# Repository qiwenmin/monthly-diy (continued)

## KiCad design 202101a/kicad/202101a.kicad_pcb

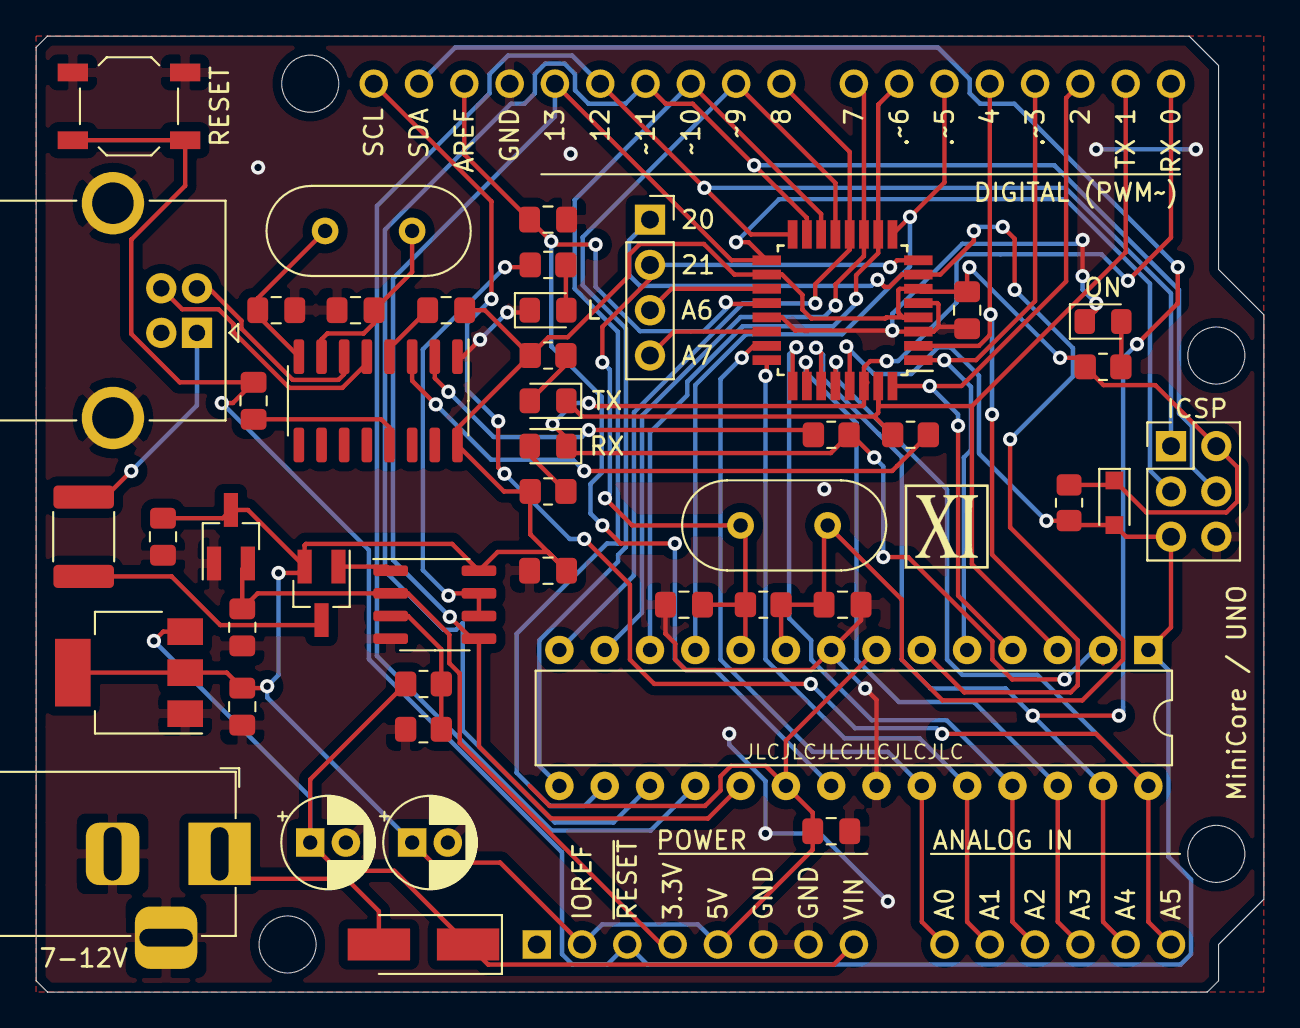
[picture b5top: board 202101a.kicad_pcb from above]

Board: 2 copper layers, 68.8 x 53.6 mm, 47 parts (1 on the bottom side), 48 nets.

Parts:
A1: Arduino_UNO_R3_BOARD; Arduino_UNO_R3_WithMountingHoles
C1, C2: 47u; CP_Radial_D5.0mm_P2.00mm
C3, C4, C5, C6, C9, C10, C11, C14, C15: 100n; C_0805_2012Metric_Pad1.18x1.45mm_HandSolder
C7, C8, C12, C13: 22p; C_0805_2012Metric_Pad1.18x1.45mm_HandSolder
D1: M7; D_SMA_Handsoldering
D2: ON; LED_0805_2012Metric_Pad1.15x1.40mm_HandSolder
D3: 1N4148WS; D_SOD-323_HandSoldering
D4: RX; LED_0805_2012Metric_Pad1.15x1.40mm_HandSolder
D5: TX; LED_0805_2012Metric_Pad1.15x1.40mm_HandSolder
D6: L; LED_0805_2012Metric_Pad1.15x1.40mm_HandSolder
F1: 500mA; Fuse_1812_4532Metric_Pad1.30x3.40mm_HandSolder
J1: Barrel_Jack_Switch; BarrelJack_Horizontal
J2: USB_B; USB_B_OST_USB-B1HSxx_Horizontal
J3: ICSP; PinHeader_2x03_P2.54mm_Vertical
J4: ExtIO; PinSocket_1x04_P2.54mm_Vertical
Q1: DMG2301L; SOT-23_Handsoldering
R1, R6, R7, R8, R9: 4.7K; R_0805_2012Metric_Pad1.20x1.40mm_HandSolder
R2, R3: 10K; R_0805_2012Metric_Pad1.20x1.40mm_HandSolder
R4, R5: 1K; R_0805_2012Metric_Pad1.20x1.40mm_HandSolder
R10: 1M; R_0805_2012Metric_Pad1.20x1.40mm_HandSolder
SW1: RESET; SW_SPST_TL3342
U1: AMS1117-5.0; SOT-223-3_TabPin2
U2: XC6206P332MR; SOT-23_Handsoldering
U3: LM358; SOIC-8_3.9x4.9mm_P1.27mm
U4: CH340G; SOIC-16_3.9x9.9mm_P1.27mm
U5: ATmega328-PU; DIP-28_W7.62mm
U6: ATmega328-AU; TQFP-32_7x7mm_P0.8mm
Y1: 12MHz; Crystal_HC49-4H_Vertical
Y2: 16MHz; Crystal_HC49-4H_Vertical

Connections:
+3V3: A1.4, C5.1, U2.2, U3.2
+5V: A1.2, A1.5, C2.1, C3.1, C4.1, C6.1, C9.1, C14.2, C15.2, D3.1, J3.2, Q1.2, R1.1, R6.1, R7.1, R8.1, U1.2, U2.3, U3.8, U4.16, U5.7, U5.20, U6.4, U6.6, U6.18
/A0: A1.9, U5.23, U6.23
/A1: A1.10, U5.24, U6.24
/A2: A1.11, U5.25, U6.25
/A3: A1.12, U5.26, U6.26
/A6: J4.3, U6.19
/A7: J4.4, U6.22
/AREF: A1.30, C11.1, U5.21, U6.20
/CMP: R2.2, R3.1, U3.3
/D0_RX: A1.15, D4.1, R4.1, U5.2, U6.30
/D1_TX: A1.16, D5.1, R5.1, U5.3, U6.31
/D2: A1.17, U5.4, U6.32
/D3: A1.18, U5.5, U6.1
/D4: A1.19, U5.6, U6.2
/D5: A1.20, U5.11, U6.9
/D6: A1.21, U5.12, U6.10
/D7: A1.22, U5.13, U6.11
/D8: A1.23, U5.14, U6.12
/D9: A1.24, U5.15, U6.13
/D10: A1.25, U5.16, U6.14
/D11: A1.26, J3.4, U5.17, U6.15
/D12: A1.27, J3.1, U5.18, U6.16
/D13: A1.28, J3.3, U3.5, U5.19, U6.17
/D20: C13.1, J4.1, R10.1, U5.9, U6.7, Y2.2
/D21: C12.1, J4.2, R10.2, U5.10, U6.8, Y2.1
/SCL_A5: A1.14, A1.32, U5.28, U6.28
/SDA_A4: A1.13, A1.31, U5.27, U6.27
/USBVCC: F1.1, Q1.3
/VIN: A1.8, C1.1, D1.1, R2.1, U1.3
/~RESET: A1.3, C10.1, D3.2, J3.5, R6.2, SW1.2, U5.1, U6.29
GND: A1.6, A1.7, A1.29, C1.2, C2.2, C3.2, C4.2, C5.2, C6.2, C7.2, C8.2, C11.2, C12.2, C13.2, C14.1, C15.1, D2.1, D6.1, J1.2, J1.3, J2.4, J2.5, J3.6, R3.2, SW1.1, U1.1, U2.1, U3.4, U4.1, U5.8, U5.22, U6.3, U6.5, U6.21
unnamed: C7.1, U4.7, Y1.1
unnamed: C8.1, U4.8, Y1.2
unnamed: C9.2, U4.4
unnamed: C10.2, U4.13
unnamed: D1.2, J1.1
unnamed: D2.2, R1.2
unnamed: D4.2, R7.2
unnamed: D5.2, R8.2
unnamed: D6.2, R9.1
unnamed: F1.2, J2.1
unnamed: J2.2, U4.6
unnamed: J2.3, U4.5
unnamed: Q1.1, U3.1
unnamed: R4.2, U4.2
unnamed: R5.2, U4.3
unnamed: R9.2, U3.6, U3.7

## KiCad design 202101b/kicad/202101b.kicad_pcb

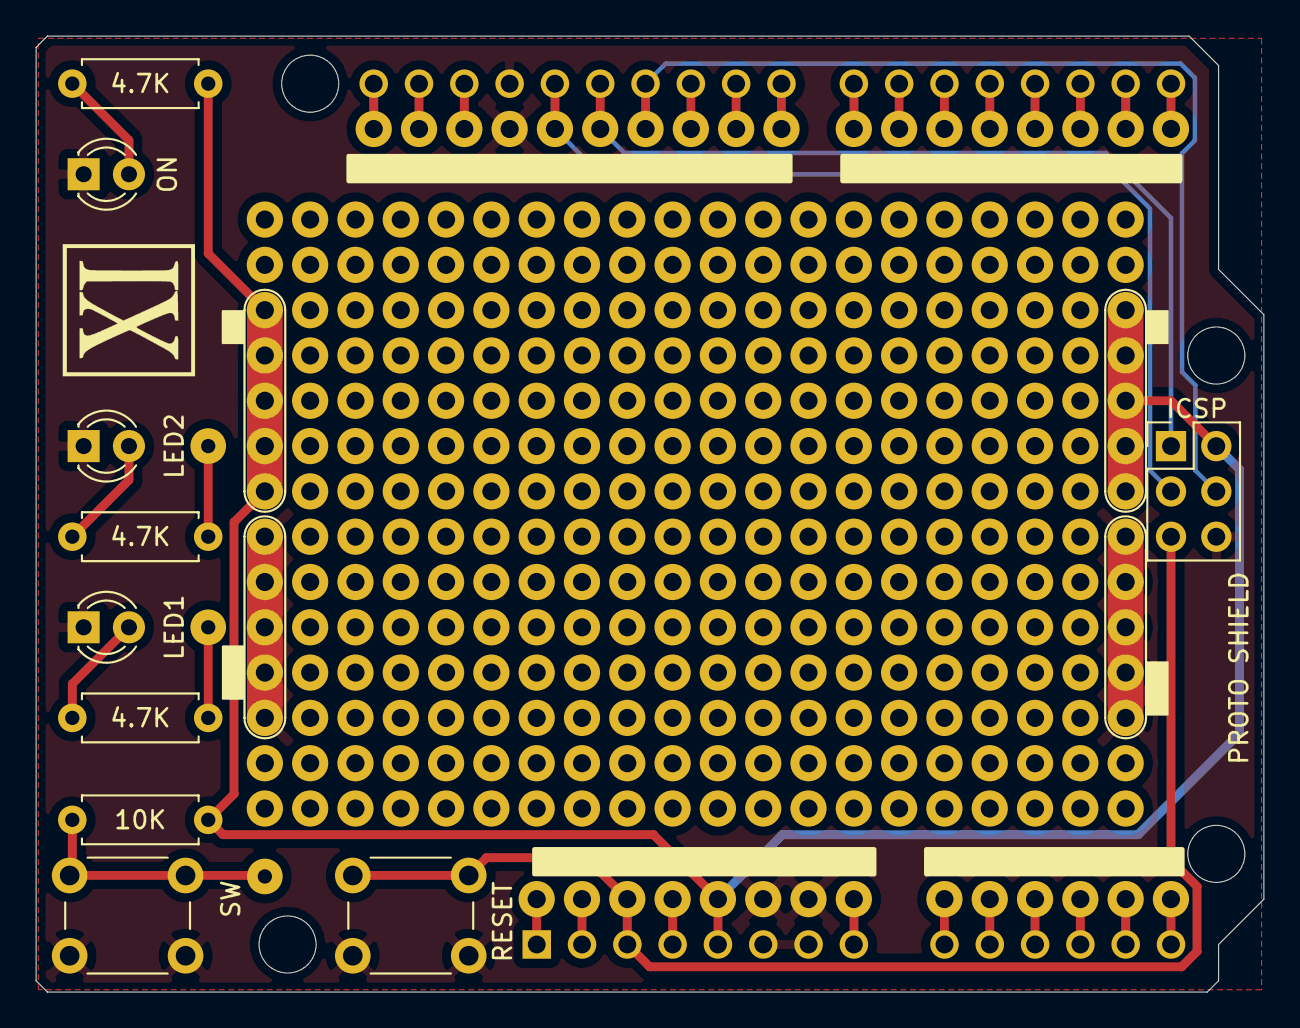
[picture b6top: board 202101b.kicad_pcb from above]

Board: 2 copper layers, 68.8 x 53.6 mm, 14 parts (1 on the bottom side), 12 nets.

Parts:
A1: Arduino_UNO_R3; Arduino_UNO_R3_WithMountingHoles
D1: ON; LED_D3.0mm
D2: LED1; LED_D3.0mm
D3: LED2; LED_D3.0mm
J1: ICSP; PinHeader_2x03_P2.54mm_Vertical
J2: LED1; FreeSolderWirePad_1x01_Drill0.8mm
J3: LED2; FreeSolderWirePad_1x01_Drill0.8mm
J4: SW; FreeSolderWirePad_1x01_Drill0.8mm
R1, R2, R3: 4.7K; R_Axial_DIN0207_L6.3mm_D2.5mm_P7.62mm_Horizontal
R4: 10K; R_Axial_DIN0207_L6.3mm_D2.5mm_P7.62mm_Horizontal
SW1: RESET; SW_PUSH_6mm
SW2: BTN; SW_PUSH_6mm

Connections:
+5V: A1.5, J1.2, R1.1, R4.1
/D11: A1.26, J1.4
/D12: A1.27, J1.1
/D13: A1.28, J1.3
/~RESET: A1.3, J1.5, SW1.2
GND: A1.6, A1.7, A1.29, D1.1, D2.1, D3.1, J1.6, SW1.1, SW2.1
unnamed: D1.2, R1.2
unnamed: D2.2, R2.2
unnamed: D3.2, R3.2
unnamed: J2.1, R2.1
unnamed: J3.1, R3.1
unnamed: J4.1, R4.2, SW2.2

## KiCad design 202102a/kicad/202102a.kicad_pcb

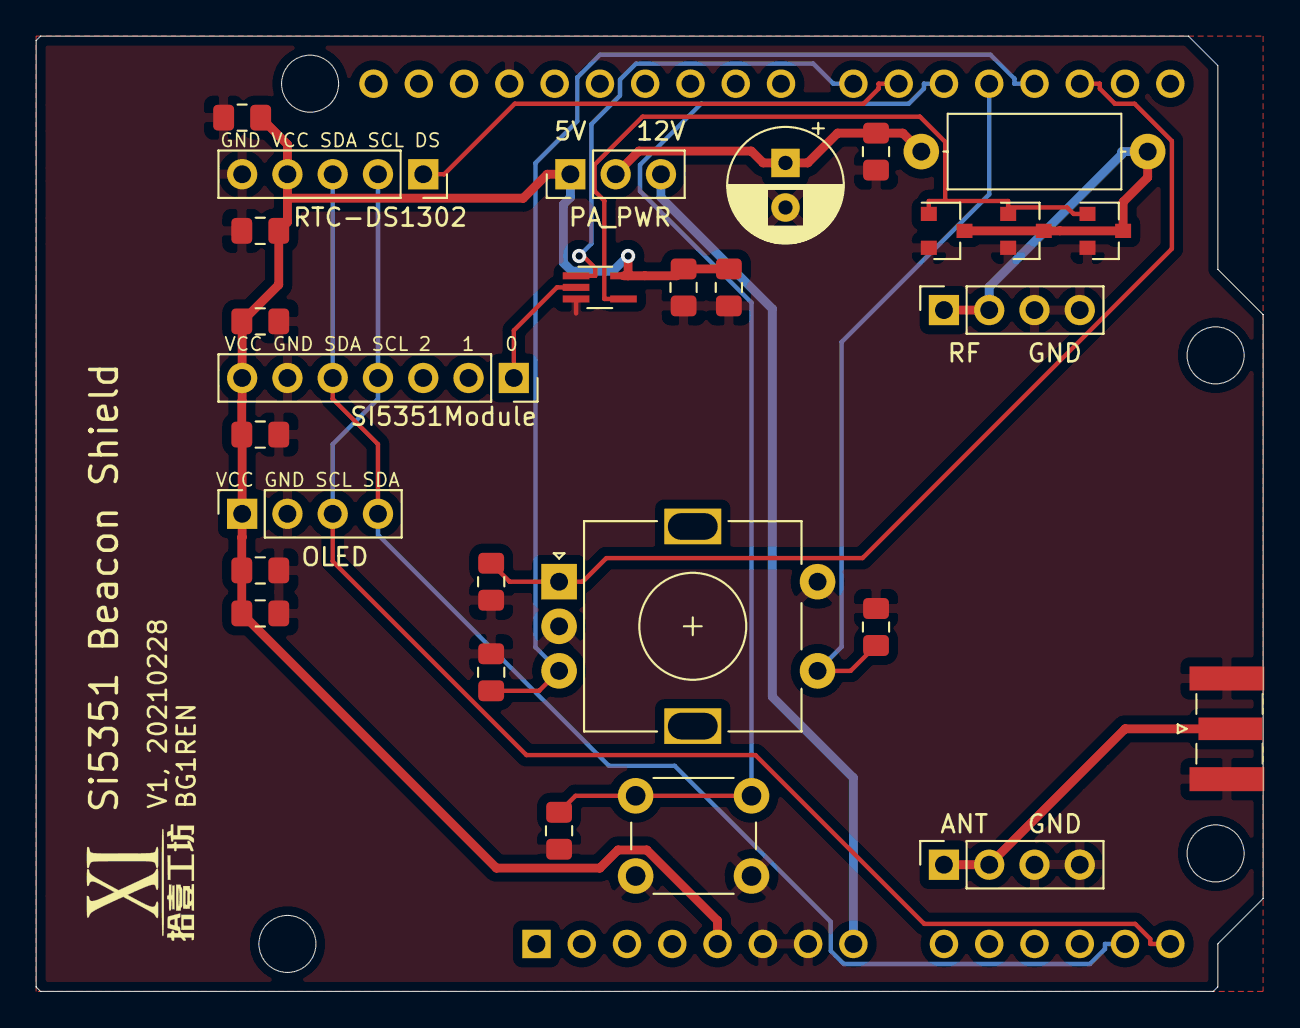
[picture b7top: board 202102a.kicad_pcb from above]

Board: 2 copper layers, 68.8 x 53.6 mm, 29 parts (1 on the bottom side), 16 nets.

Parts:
A1: Shield; Arduino_UNO_R3_WithMountingHoles
C1, C2, C4, C6, C8, C10, C12, C13, C14: 10n; C_0805_2012Metric_Pad1.18x1.45mm_HandSolder
C3, C5, C7, C9: 1u; C_0805_2012Metric_Pad1.18x1.45mm_HandSolder
C11: 100u; CP_Radial_D6.3mm_P2.50mm
J1: ANT; SMA_Samtec_SMA-J-P-X-ST-EM1_EdgeMount
J2: LPF_A; PinSocket_1x04_P2.54mm_Vertical
J3: LPF_B; PinSocket_1x04_P2.54mm_Vertical
J4: SI5351Module; PinSocket_1x07_P2.54mm_Vertical
J5: OLED; PinSocket_1x04_P2.54mm_Vertical
J6: PA_PWR; PinHeader_1x03_P2.54mm_Vertical
J7: RTC-DS1302; PinSocket_1x05_P2.54mm_Vertical
L1: 100u; L_Axial_L9.5mm_D4.0mm_P12.70mm_Horizontal_Fastron_SMCC
Q1, Q2, Q3: 2N7002K; SOT-23
SW1: Encoder; RotaryEncoder_Alps_EC11E-Switch_Vertical_H20mm
SW2: L_BTN; SW_PUSH_6mm
U1: 74LVC1G08; SOT-353_SC-70-5_Handsoldering

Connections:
+12V: A1.8, J6.3
ANT: J1.1, J2.1, J2.2
CLK0: J4.1, U1.2
C_OUT: Q1.1, Q2.1, Q3.1, U1.4
DS: A1.21, J7.1
GND: A1.6, A1.7, A1.29, C1.2, C2.2, C3.2, C4.2, C5.2, C6.2, C7.2, C8.2, C9.2, C10.2, C11.2, C12.2, C13.2, C14.2, J1.2, J2.3, J2.4, J3.3, J3.4, J4.6, J5.2, J7.5, Q1.2, Q2.2, Q3.2, SW1.C, SW1.S2, SW2.1, U1.3
PA_PWR: C11.1, C12.1, J6.2, L1.1
RF_OUT: J3.1, J3.2, L1.2, Q1.3, Q2.3, Q3.3
ROT_1: A1.17, C1.1, SW1.A
ROT_2: A1.18, C2.1, SW1.B
SCL: A1.14, J4.4, J5.3, J7.2
SDA: A1.13, J4.5, J5.4, J7.3
SW_BTN: A1.20, C13.1, SW2.2
SW_R: A1.19, C14.1, SW1.S1
TX: A1.22, U1.1
VCC: A1.5, C3.1, C4.1, C5.1, C6.1, C7.1, C8.1, C9.1, C10.1, J4.7, J5.1, J6.1, J7.4, U1.5

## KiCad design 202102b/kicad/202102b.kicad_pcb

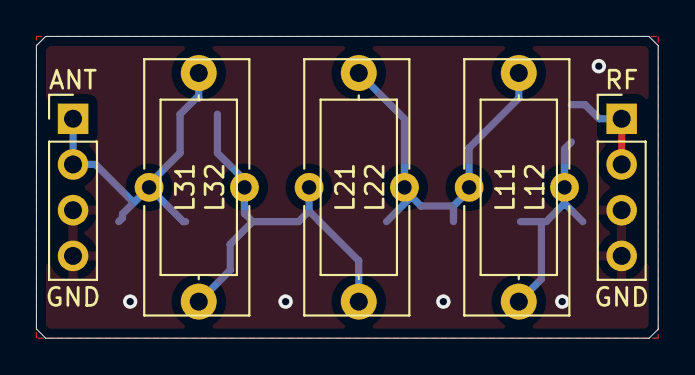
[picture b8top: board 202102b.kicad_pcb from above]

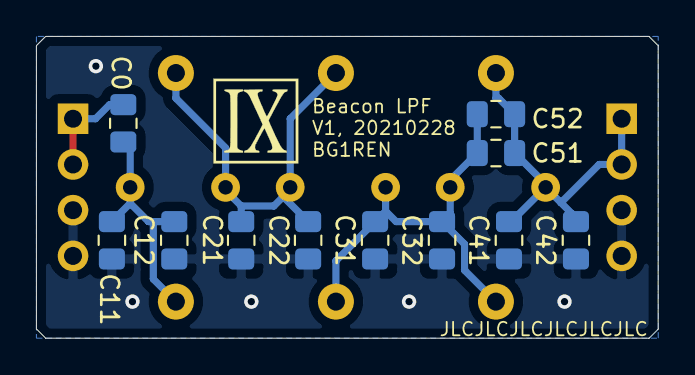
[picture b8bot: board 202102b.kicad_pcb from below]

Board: 2 copper layers, 34.5 x 16.8 mm, 19 parts (11 on the bottom side), 6 nets.

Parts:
C0: 100n; C_0805_2012Metric_Pad1.18x1.45mm_HandSolder
C11, C12, C21, C22, C31, C32, C41, C42: 220p; C_0805_2012Metric_Pad1.18x1.45mm_HandSolder
C51, C52: 47p; C_0805_2012Metric_Pad1.18x1.45mm_HandSolder
J1: LPF_A; PinHeader_1x04_P2.54mm_Vertical
J2: LPF_B; PinHeader_1x04_P2.54mm_Vertical
L11, L21, L31: 1u; L_Axial_L9.5mm_D4.0mm_P12.70mm_Horizontal_Fastron_SMCC
L12, L22, L32: 1u; L_Toroid_Vertical_L14.0mm_W5.6mm_P5.30mm_Bourns_5700

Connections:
ANT: C41.2, C42.2, C51.1, C52.1, J1.1, J1.2, L31.2, L32.2
GND: C11.1, C12.1, C21.1, C22.1, C31.1, C32.1, C41.1, C42.1, J1.3, J1.4, J2.3, J2.4
unnamed: C0.1, C11.2, C12.2, L11.1, L12.1
unnamed: C21.2, C22.2, L11.2, L12.2, L21.1, L22.1
unnamed: C31.2, C32.2, C51.2, C52.2, L21.2, L22.2, L31.1, L32.1
RF: C0.2, J2.1, J2.2
